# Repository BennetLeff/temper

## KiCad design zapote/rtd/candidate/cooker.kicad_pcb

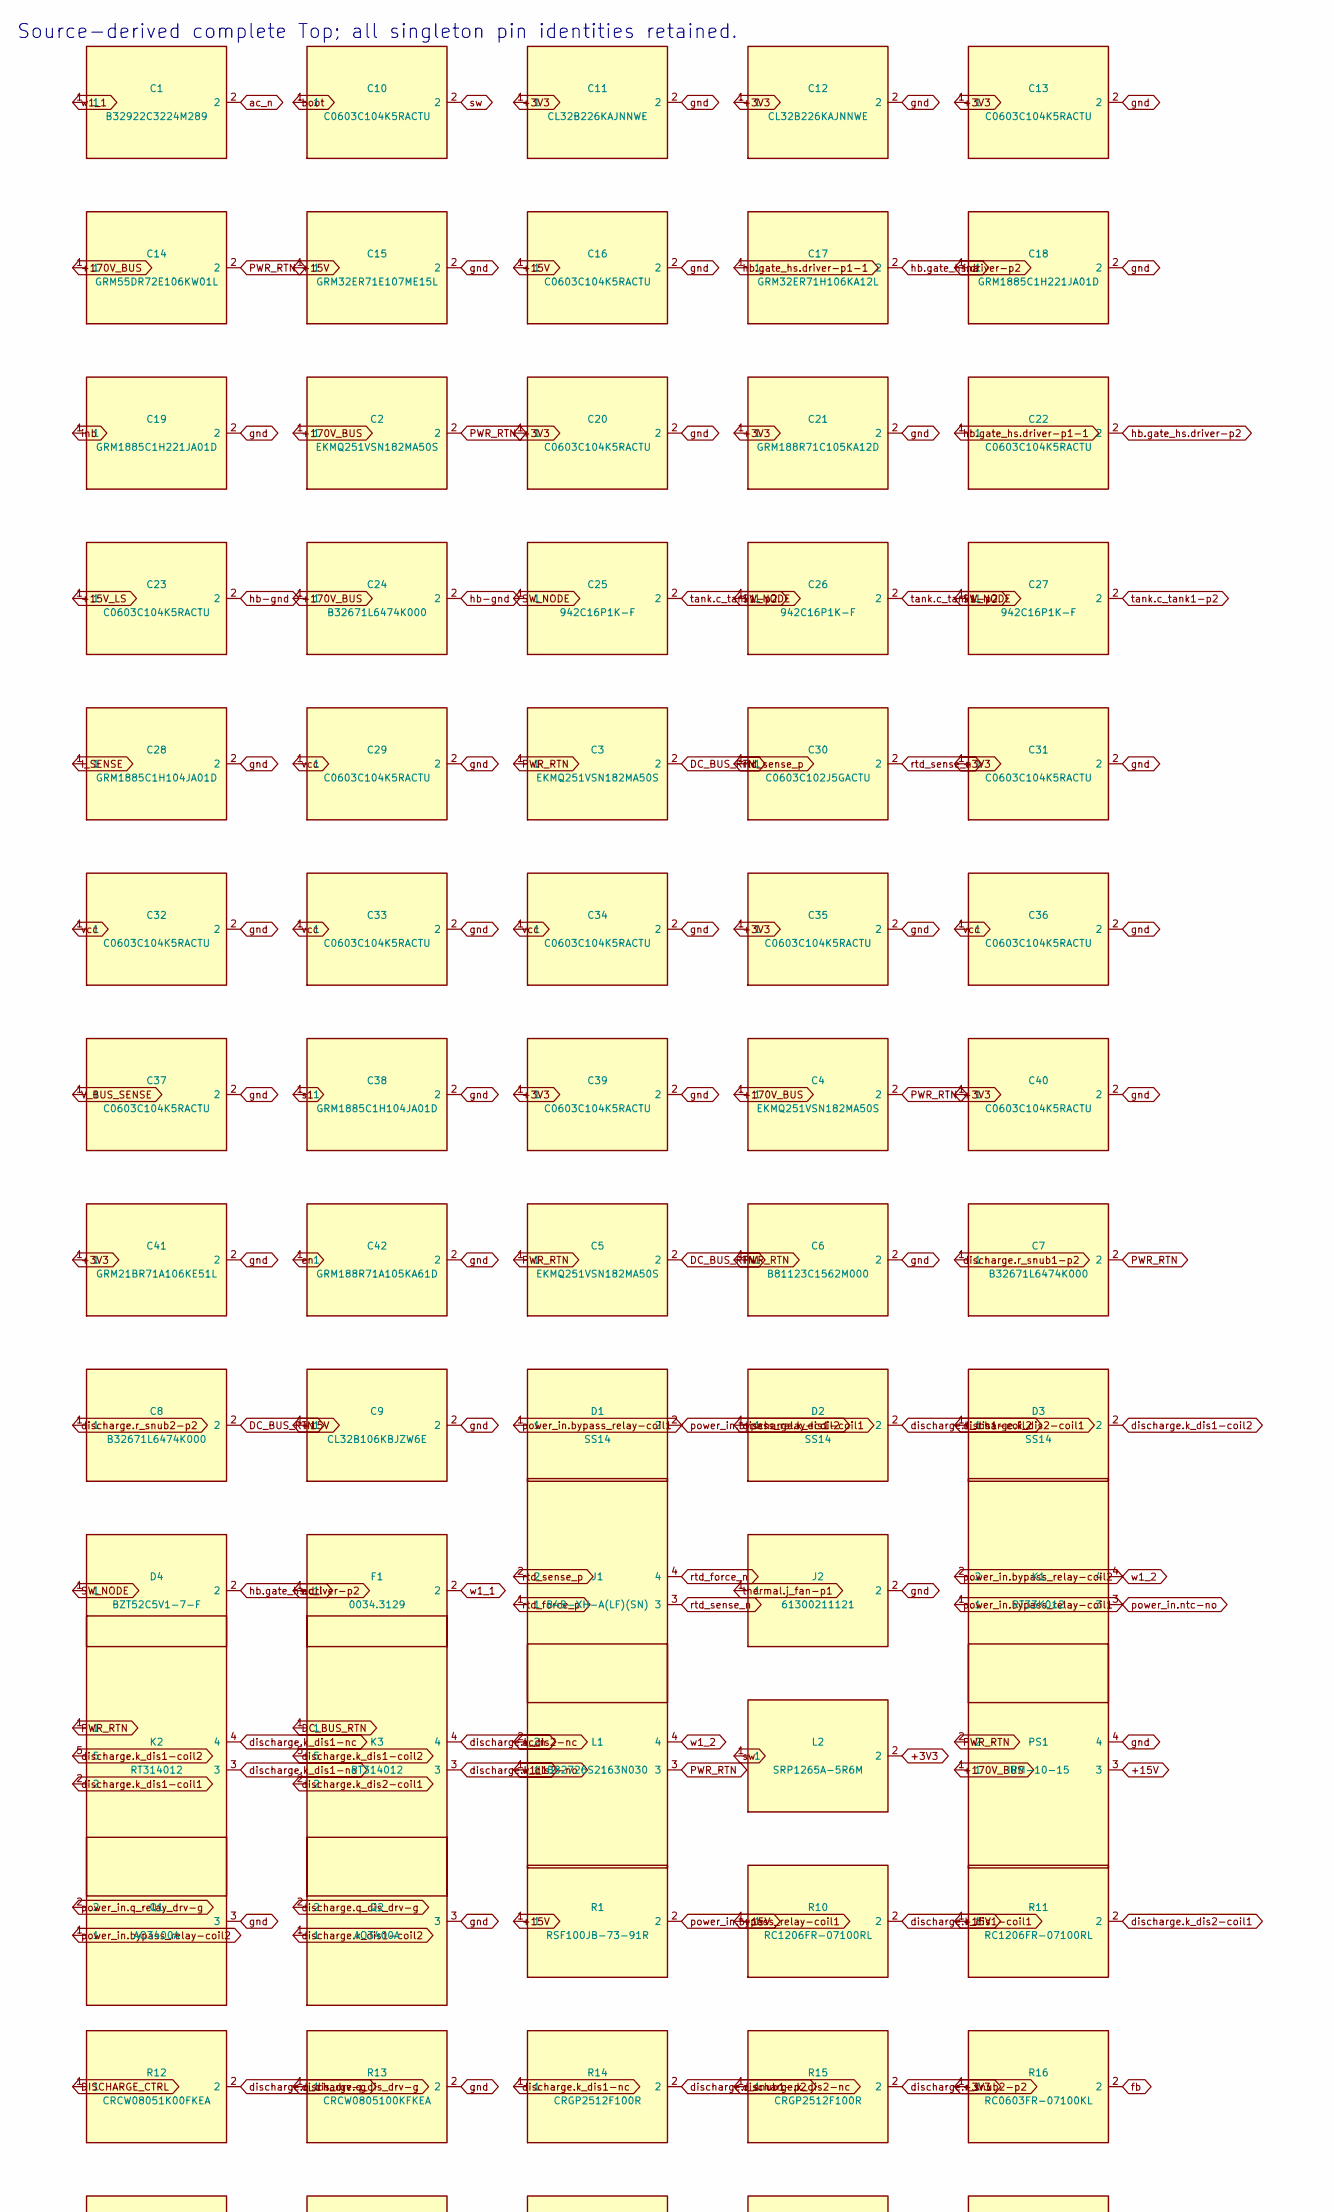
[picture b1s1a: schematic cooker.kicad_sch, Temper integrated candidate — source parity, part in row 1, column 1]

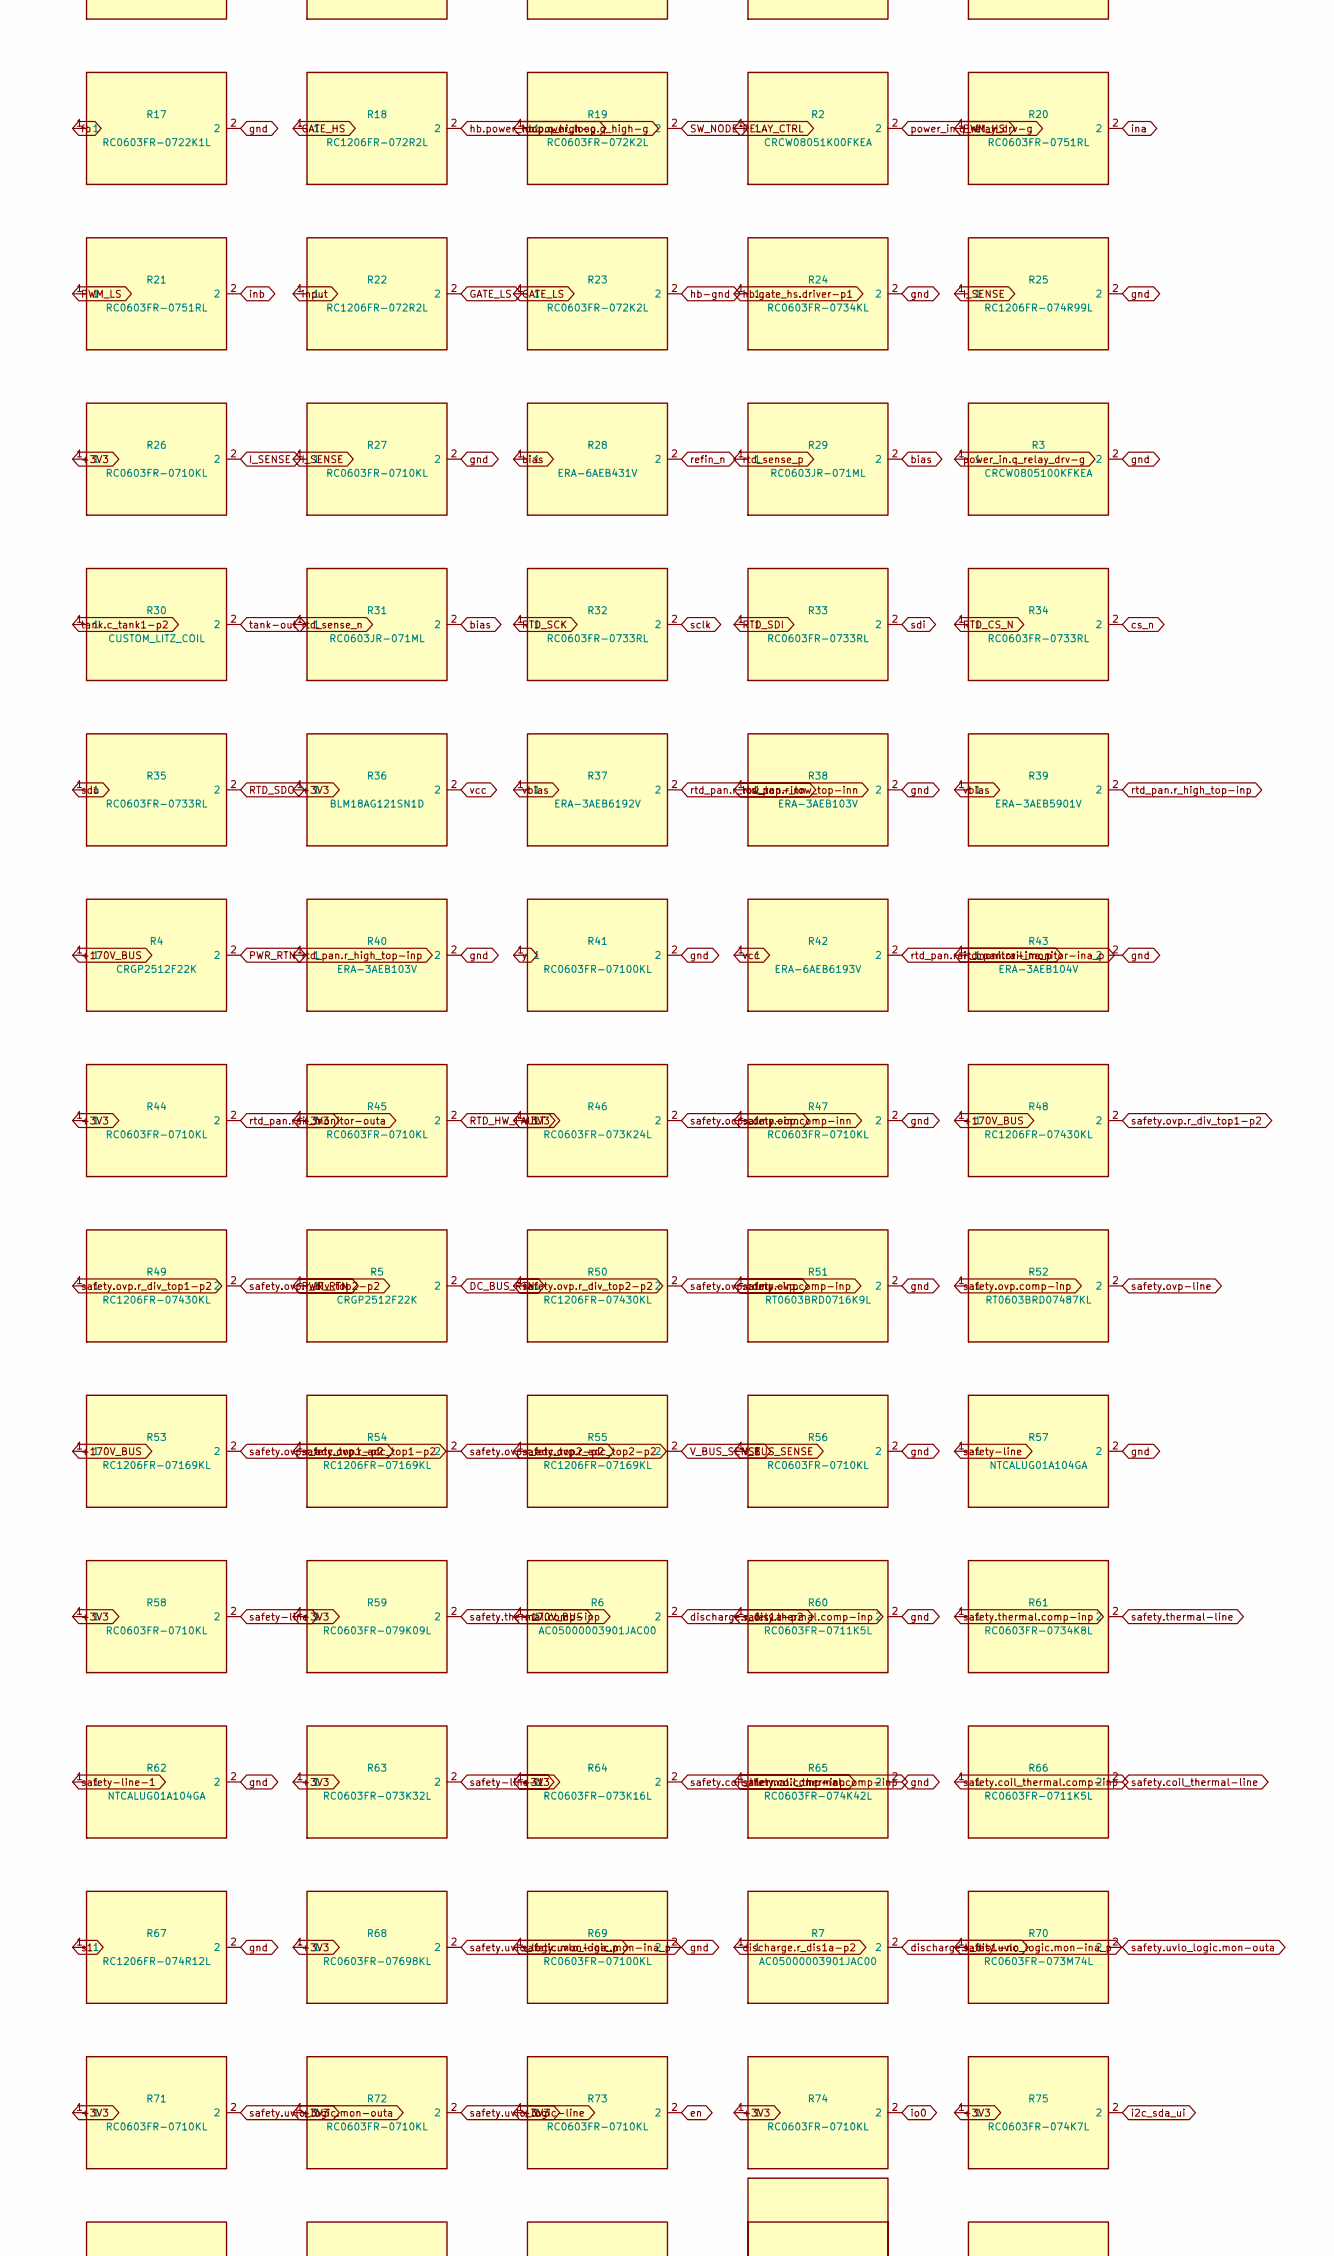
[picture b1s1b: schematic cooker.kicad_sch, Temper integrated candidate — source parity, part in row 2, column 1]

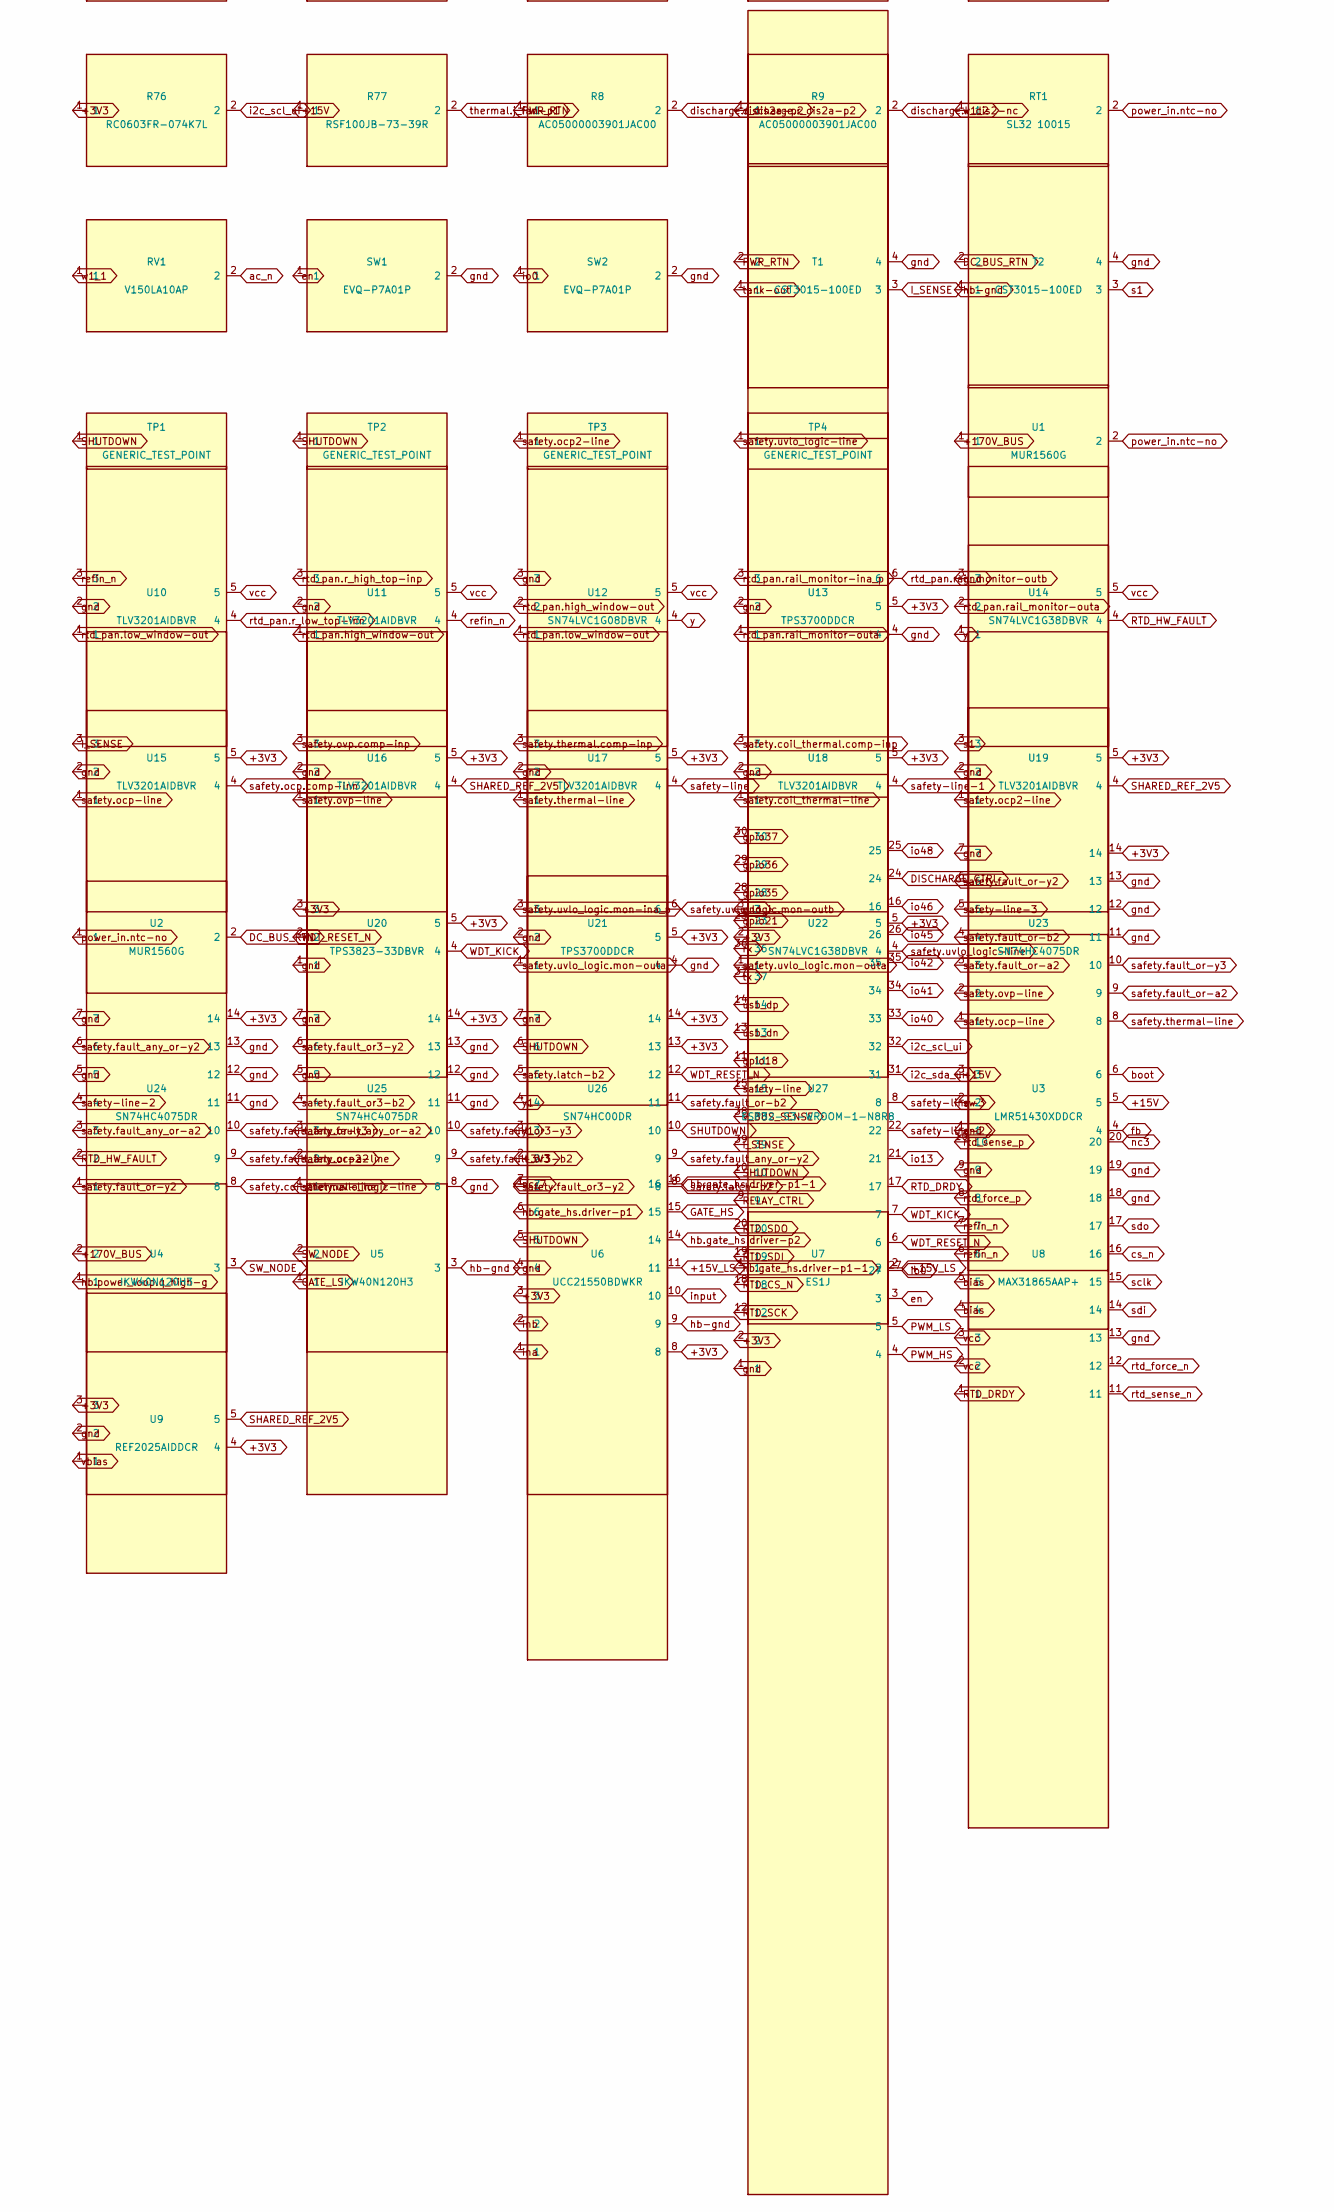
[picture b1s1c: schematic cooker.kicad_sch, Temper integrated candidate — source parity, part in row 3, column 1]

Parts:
C1: B32922C3224M289; C_Rect_L18.0mm_W7.0mm_P15.00mm_FKS3_FKP3
C2, C3, C4, C5: EKMQ251VSN182MA50S; CP_Radial_D35.0mm_P10.00mm_SnapIn
C6: B81123C1562M000; C_Rect_L26.5mm_W7.0mm_P22.50mm_MKS4
C7, C8, C24: B32671L6474K000; C_Rect_L18.0mm_W11.0mm_P15.00mm_FKS3_FKP3
C9: CL32B106KBJZW6E; C_1210_3225Metric
C10, C13, C16, C20, C22, C23, C29, C31, C32, C33, C34, C35, C36, C37, C39, C40: C0603C104K5RACTU; C_0603_1608Metric
C11, C12: CL32B226KAJNNWE; C_1210_3225Metric
C14: GRM55DR72E106KW01L; C_2220_5750Metric
C15: GRM32ER71E107ME15L; C_1210_3225Metric
C17: GRM32ER71H106KA12L; C_1210_3225Metric
C18, C19: GRM1885C1H221JA01D; C_0603_1608Metric
C21: GRM188R71C105KA12D; C_0603_1608Metric
C25, C26, C27: 942C16P1K-F; C_Axial_L34.0mm_D22.5mm_P40.00mm_Horizontal
C28, C38: GRM1885C1H104JA01D; C_0603_1608Metric
C30: C0603C102J5GACTU; C_0603_1608Metric
C41: GRM21BR71A106KE51L; C_0805_2012Metric
C42: GRM188R71A105KA61D; C_0603_1608Metric
D1, D2, D3: SS14; D_SMA
D4: BZT52C5V1-7-F; D_SOD-123
F1: 0034.3129; Fuse_Holder_5x20mm
J1: B4B-XH-A(LF)(SN); JST_XH_B4B-XH-A_1x04_P2.50mm_Vertical
J2: 61300211121; PinHeader_1x02_P2.54mm_Vertical
K1: RT33K012; Relay_SPST_Schrack-RT33K012
K2, K3: RT314012; Relay_SPDT_Schrack-RT314012
L1: B82726S2163N030; CMC_B82726S
L2: SRP1265A-5R6M; L_Bourns_SRP1265A
PS1: IRM-10-15; Converter_ACDC_MeanWell_IRM-10-xx_THT
Q1, Q2: AO3400A; SOT-23
R1: RSF100JB-73-91R; R_Axial_DIN0207_L6.3mm_D2.5mm_P10.16mm_Horizontal
R2, R12: CRCW08051K00FKEA; R_0805_2012Metric
R3, R13: CRCW0805100KFKEA; R_0805_2012Metric
R4, R5: CRGP2512F22K; R_2512_6332Metric
R6, R7, R8, R9: AC05000003901JAC00; R_Axial_DIN0918_L18.0mm_D9.0mm_P22.86mm_Horizontal
R10, R11: RC1206FR-07100RL; R_1206_3216Metric
R14, R15: CRGP2512F100R; R_2512_6332Metric
R16, R41, R69: RC0603FR-07100KL; R_0603_1608Metric
R17: RC0603FR-0722K1L; R_0603_1608Metric
R18, R22: RC1206FR-072R2L; R_1206_3216Metric
R19, R23: RC0603FR-072K2L; R_0603_1608Metric
R20, R21: RC0603FR-0751RL; R_0603_1608Metric
R24: RC0603FR-0734KL; R_0603_1608Metric
R25: RC1206FR-074R99L; R_1206_3216Metric
R26, R27, R44, R45, R47, R56, R58, R71, R72, R73, R74: RC0603FR-0710KL; R_0603_1608Metric
R28: ERA-6AEB431V; R_0805_2012Metric
R29, R31: RC0603JR-071ML; R_0603_1608Metric
R30: CUSTOM_LITZ_COIL; LitzPad_15A
R32, R33, R34, R35: RC0603FR-0733RL; R_0603_1608Metric
R36: BLM18AG121SN1D; L_0603_1608Metric
R37: ERA-3AEB6192V; R_0603_1608Metric
R38, R40: ERA-3AEB103V; R_0603_1608Metric
R39: ERA-3AEB5901V; R_0603_1608Metric
R42: ERA-6AEB6193V; R_0805_2012Metric
R43: ERA-3AEB104V; R_0603_1608Metric
R46: RC0603FR-073K24L; R_0603_1608Metric
R48, R49, R50: RC1206FR-07430KL; R_1206_3216Metric
R51: RT0603BRD0716K9L; R_0603_1608Metric
R52: RT0603BRD07487KL; R_0603_1608Metric
R53, R54, R55: RC1206FR-07169KL; R_1206_3216Metric
R57: NTCALUG01A104GA; R_Axial_DIN0204_L3.6mm_D1.6mm_P2.54mm_Vertical
R59: RC0603FR-079K09L; R_0603_1608Metric
R60, R66: RC0603FR-0711K5L; R_0603_1608Metric
R61: RC0603FR-0734K8L; R_0603_1608Metric
R62: NTCALUG01A104GA; R_Axial_DIN0207_L6.3mm_D2.5mm_P10.16mm_Horizontal
R63: RC0603FR-073K32L; R_0603_1608Metric
R64: RC0603FR-073K16L; R_0603_1608Metric
R65: RC0603FR-074K42L; R_0603_1608Metric
R67: RC1206FR-074R12L; R_1206_3216Metric
R68: RC0603FR-07698KL; R_0603_1608Metric
R70: RC0603FR-073M74L; R_0603_1608Metric
R75, R76: RC0603FR-074K7L; R_0603_1608Metric
R77: RSF100JB-73-39R; R_Axial_DIN0207_L6.3mm_D2.5mm_P10.16mm_Horizontal
RT1: SL32 10015; R_Disc_D15.0mm_W7.0mm_P7.5mm
RV1: V150LA10AP; RV_Disc_D15.5mm_W5.2mm_P7.5mm
SW1, SW2: EVQ-P7A01P; SW_SPST_EVQP7A
T1, T2: CST3015-100ED; CST3015
TP1, TP2, TP3, TP4: GENERIC_TEST_POINT; TestPoint_Pad_D1.0mm
U1, U2: MUR1560G; TO-220-2_Vertical
U3: LMR51430XDDCR; SOT-23-6
U4, U5: IKW40N120H3; TO-247-3_Vertical
U6: UCC21550BDWKR; SOIC16W_Isolated
U7: ES1J; D_SMA
U8: MAX31865AAP+; SSOP-20_3.9x8.7mm_P0.635mm
U9: REF2025AIDDCR; SOT-23-5
U10, U11, U15, U16, U17, U18, U19: TLV3201AIDBVR; SOT-23-5
U12: SN74LVC1G08DBVR; SOT-23-5
U13, U21: TPS3700DDCR; SOT-23-6
U14, U22: SN74LVC1G38DBVR; SOT-23-5
U20: TPS3823-33DBVR; SOT-23-5
U23, U24, U25: SN74HC4075DR; SOIC-14_3.9x8.7mm_P1.27mm
U26: SN74HC00DR; SOIC-14_3.9x8.7mm_P1.27mm
U27: ESP32-S3-WROOM-1-N8R8; ESP32-S3-WROOM-1

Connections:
+3V3: C11.1, C12.1, C13.1, C20.1, C21.1, C31.1, C35.1, C39.1, C40.1, C41.1, L2.2, R16.1, R26.1, R36.1, R44.1, R45.1, R46.1, R58.1, R59.1, R63.1, R64.1, R68.1, R71.1, R72.1, R73.1, R74.1, R75.1, R76.1, U6.3, U6.8, U9.3, U9.4, U13.5, U15.5, U16.5, U17.5, U18.5, U19.5, U20.3, U20.5, U21.5, U22.2, U22.5, U23.14, U24.14, U25.14, U26.2, U26.13, U26.14, U27.2
+15V: C9.1, C15.1, C16.1, PS1.3, R1.1, R10.1, R11.1, R77.1, U3.3, U3.5
+15V_LS: C23.1, U6.11, U7.2
+170V_BUS: C2.1, C4.1, C14.1, C24.1, PS1.1, R4.1, R6.1, R48.1, R53.1, U1.1, U4.2
DC_BUS_RTN: C3.2, C5.2, C8.2, K3.1, R5.2, T2.2, U2.2
DISCHARGE_CTRL: R12.1, U27.24
GATE_HS: R18.1, U6.15
GATE_LS: R22.2, R23.1, U5.1
I_SENSE: C28.1, R25.1, R26.2, R27.1, T1.3, U15.3, U27.39
PWM_HS: R20.1, U27.4
PWM_LS: R21.1, U27.5
PWR_RTN: C2.2, C3.1, C4.2, C5.1, C6.1, C7.2, C14.2, K2.1, L1.3, PS1.2, R4.2, R5.1, R8.1, T1.2
RELAY_CTRL: R2.1, U27.9
RTD_CS_N: R34.1, U27.18
RTD_DRDY: U8.1, U27.17
RTD_HW_FAULT: R45.2, U14.4, U24.2
RTD_SCK: R32.1, U27.12
RTD_SDI: R33.1, U27.19
RTD_SDO: R35.2, U27.20
SHARED_REF_2V5: U9.5, U16.4, U19.4
SHUTDOWN: TP1.1, TP2.1, U6.5, U26.6, U26.10, U27.10
SW_NODE: C25.1, C26.1, C27.1, D4.1, R19.2, U4.3, U5.2
V_BUS_SENSE: C37.1, R55.2, R56.1, U27.38
WDT_KICK: U20.4, U27.7
WDT_RESET_N: U20.2, U26.12, U27.6
ac_l: F1.1
ac_n: C1.2, L1.2, RV1.2
bias: R28.1, R29.2, R31.2, U8.4, U8.5
boot: C10.1, U3.6
cs_n: R34.2, U8.16
discharge.k_dis1-coil1: D2.1, K2.2, R10.2
discharge.k_dis1-coil2: D2.2, D3.2, K2.5, K3.5, Q2.1
discharge.k_dis1-nc: K2.4, R7.2, R14.1
discharge.k_dis1-no: K2.3
discharge.k_dis2-coil1: D3.1, K3.2, R11.2
discharge.k_dis2-nc: K3.4, R9.2, R15.1
discharge.k_dis2-no: K3.3
discharge.q_dis_drv-g: Q2.2, R12.2, R13.1
discharge.r_dis1a-p2: R6.2, R7.1
discharge.r_dis2a-p2: R8.2, R9.1
discharge.r_snub1-p2: C7.1, R14.2
discharge.r_snub2-p2: C8.1, R15.2
en: C42.1, R73.2, SW1.1, U27.3
fb: R16.2, R17.1, U3.4
gnd: C6.2, C9.2, C11.2, C12.2, C13.2, C15.2, C16.2, C18.2, C19.2, C20.2, C21.2, C28.2, C29.2, C31.2, C32.2, C33.2, C34.2, C35.2, C36.2, C37.2, C38.2, C39.2, C40.2, C41.2, C42.2, J2.2, PS1.4, Q1.3, Q2.3, R3.2, R13.2, R17.2, R24.2, R25.2, R27.2, R38.2, R40.2, R41.2, R43.2, R47.2, R51.2, R56.2, R57.2, R60.2, R62.2, R65.2, R67.2, R69.2, SW1.2, SW2.2, T1.4, T2.4, U3.1, U6.4, U8.9, U8.13, U8.18, U8.19, U9.2, U10.2, U11.2, U12.3, U13.2, U13.4, U14.3, U15.2, U16.2, U17.2, U18.2, U19.2, U20.1, U21.2, U21.4, U22.3, U23.7, U23.11, U23.12, U23.13, U24.5, U24.7, U24.11, U24.12, U24.13, U25.5, U25.7, U25.8, U25.11, U25.12, U25.13, U26.7, U27.1
gpio18: U27.11
gpio21: U27.23
gpio35: U27.28
gpio36: U27.29
gpio37: U27.30
hb-gnd: C23.2, C24.2, R23.2, T2.1, U5.3, U6.9
hb.gate_hs.driver-p1: R24.1, U6.6
hb.gate_hs.driver-p1-1: C17.1, C22.1, U6.16, U7.1
hb.gate_hs.driver-p2: C17.2, C22.2, D4.2, U6.14
hb.power_loop.q_high-g: R18.2, R19.1, U4.1
i2c_scl_ui: R76.2, U27.32
i2c_sda_ui: R75.2, U27.31
ina: C18.1, R20.2, U6.1
inb: C19.1, R21.2, U6.2
input: R22.1, U6.10
io0: R74.2, SW2.1, U27.27
io13: U27.21
io40: U27.33
io41: U27.34
io42: U27.35
io45: U27.26
io46: U27.16
io48: U27.25
nc3: U8.20
nc_7: U6.7
power_in.bypass_relay-coil1: D1.1, K1.1, R1.2
power_in.bypass_relay-coil2: D1.2, K1.2, Q1.1
power_in.ntc-no: K1.3, RT1.2, U1.2, U2.1
power_in.q_relay_drv-g: Q1.2, R2.2, R3.1
refin_n: R28.2, U8.6, U8.7, U10.3, U11.4
rtd_force_n: J1.4, U8.12
rtd_force_p: J1.1, U8.8
rtd_pan.high_window-out: U11.1, U12.2
rtd_pan.low_window-out: U10.1, U12.1
rtd_pan.r_high_top-inp: R39.2, R40.1, U11.3
rtd_pan.r_low_top-inn: R37.2, R38.1, U10.4
rtd_pan.rail_monitor-ina_p: R42.2, R43.1, U13.3
rtd_pan.rail_monitor-outa: R44.2, U13.1, U14.2
rtd_pan.rail_monitor-outb: U13.6
rtd_sense_n: C30.2, J1.3, R31.1, U8.11
rtd_sense_p: C30.1, J1.2, R29.1, U8.10
rx: U27.36
s1: C38.1, R67.1, T2.3, U19.3
safety-line: R57.1, R58.2, U17.4, U27.15
safety-line-1: R62.1, R63.2, U18.4
safety-line-2: U24.4, U27.22
safety-line-3: U23.5, U27.8
safety.coil_thermal-line: R66.2, U18.1, U24.8
safety.coil_thermal.comp-inp: R64.2, R65.1, R66.1, U18.3
safety.fault_any_or-a2: U24.3, U24.9, U25.3
safety.fault_any_or-y2: U24.6, U26.9
safety.fault_any_or-y3: U24.10
safety.fault_or3-b2: U25.4, U25.9
safety.fault_or3-y2: U25.6, U26.1
safety.fault_or3-y3: U25.10
safety.fault_or-a2: U23.3, U23.9
safety.fault_or-b2: U23.4, U26.11
safety.fault_or-y2: U23.6, U24.1
safety.fault_or-y3: U23.10
safety.latch-b2: U26.5, U26.8
safety.ocp2-line: TP3.1, U19.1, U25.2
safety.ocp-line: U15.1, U23.1
safety.ocp.comp-inn: R46.2, R47.1, U15.4
safety.ovp-line: R52.2, U16.1, U23.2
safety.ovp.comp-inp: R50.2, R51.1, R52.1, U16.3
safety.ovp.r_adc_top1-p2: R53.2, R54.1
safety.ovp.r_adc_top2-p2: R54.2, R55.1
safety.ovp.r_div_top1-p2: R48.2, R49.1
safety.ovp.r_div_top2-p2: R49.2, R50.1
safety.thermal-line: R61.2, U17.1, U23.8
safety.thermal.comp-inp: R59.2, R60.1, R61.1, U17.3
safety.uvlo_logic-line: R72.2, TP4.1, U22.4, U25.1
safety.uvlo_logic.mon-ina_p: R68.2, R69.1, R70.1, U21.3
safety.uvlo_logic.mon-outa: R70.2, R71.2, U21.1, U22.1
safety.uvlo_logic.mon-outb: U21.6
sclk: R32.2, U8.15
sdi: R33.2, U8.14
sdo: R35.1, U8.17
sw: C10.2, L2.1, U3.2
tank-out: R30.2, T1.1
tank.c_tank1-p2: C25.2, C26.2, C27.2, R30.1
thermal.j_fan-p1: J2.1, R77.2
tx: U27.37
usb_dn: U27.13
usb_dp: U27.14
vbias: R37.1, R39.1, U9.1
vcc: C29.1, C32.1, C33.1, C34.1, C36.1, R36.2, R42.1, U8.2, U8.3, U10.5, U11.5, U12.5, U14.5
w1_1: C1.1, F1.2, L1.1, RV1.1
w1_2: K1.4, L1.4, RT1.1
y: R41.1, U12.4, U14.1
y1: U26.3, U26.4

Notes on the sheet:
Source-derived complete Top; all singleton pin identities retained.

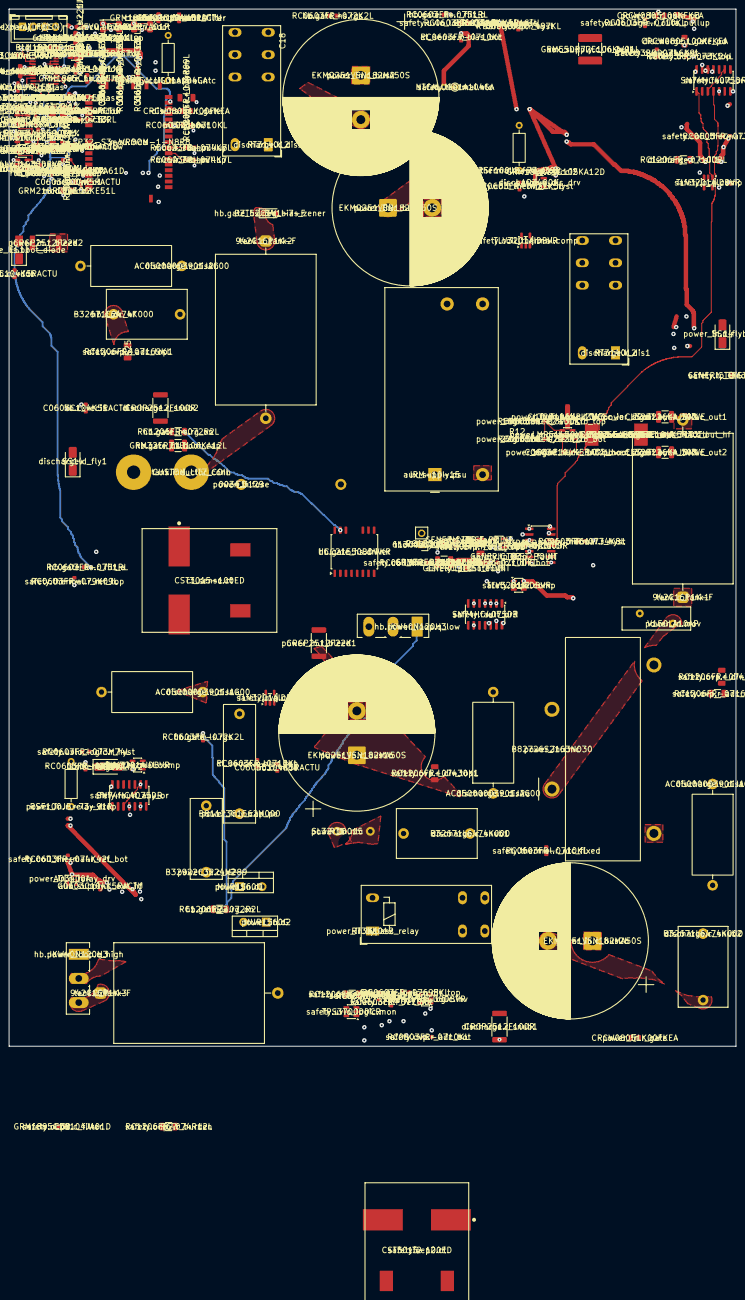
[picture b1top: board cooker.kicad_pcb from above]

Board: 6 copper layers, 164.0 x 234.0 mm, 171 parts (0 on the bottom side), 110 nets.

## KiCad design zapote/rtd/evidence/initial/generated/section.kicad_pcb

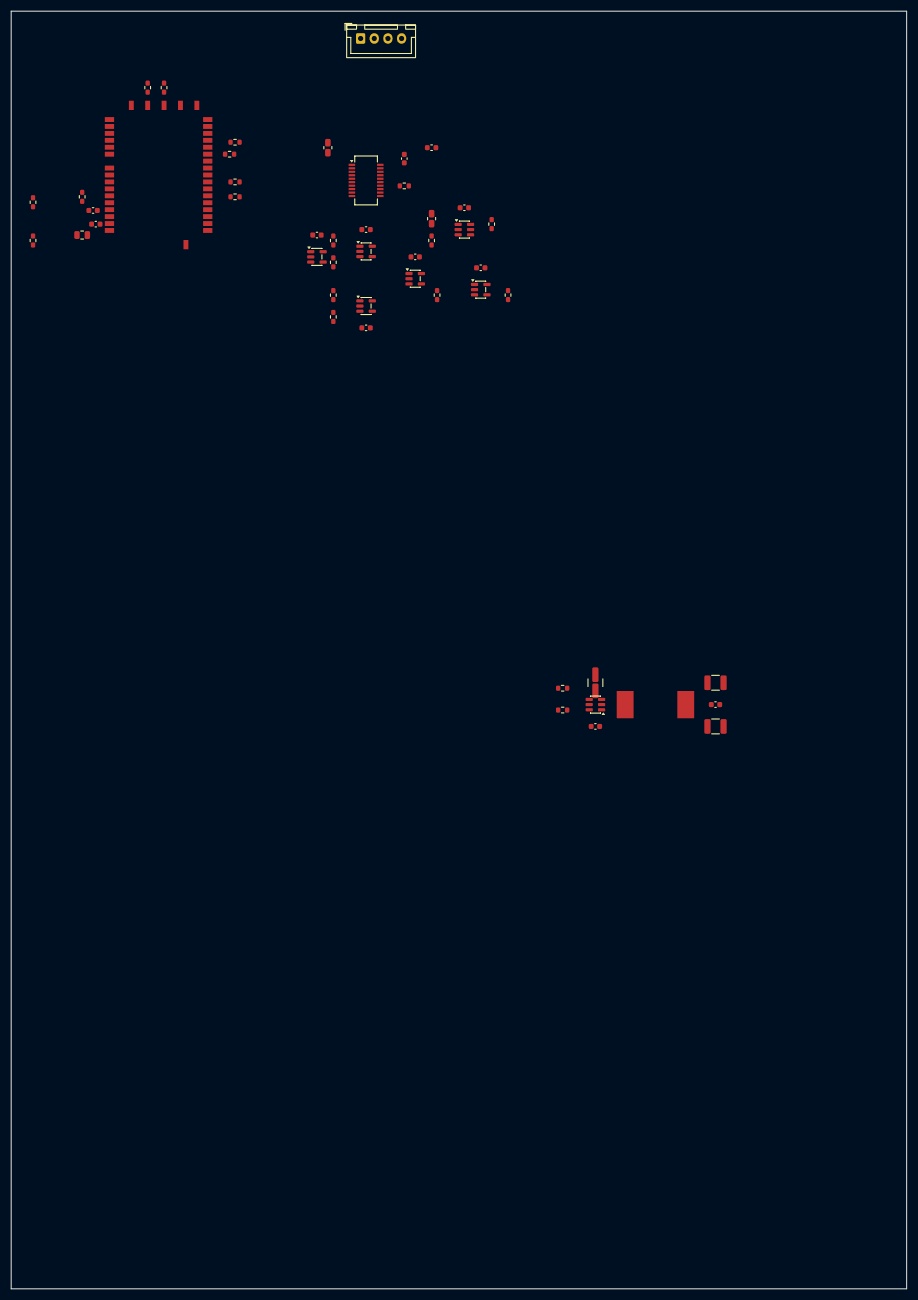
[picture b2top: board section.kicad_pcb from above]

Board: 6 copper layers, 164.0 x 234.0 mm, 49 parts (0 on the bottom side), 35 nets, no tracks yet.

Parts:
C9: 10uF +/- 10%; C_1210_3225Metric
C10, C13: 100nF +/- 10%; C_0603_1608Metric
C11, C12: 22uF +/- 10%; C_1210_3225Metric
C29, C30, C31, C32, C33, C34, C35, C39: 100nF; C_0603_1608Metric
C40: 10uF; C_0805_2012Metric
C41: 1uF +/- 10%; C_0603_1608Metric
J1: B4B-XH-A(LF)(SN); JST_XH_B4B-XH-A_1x04_P2.50mm_Vertical
L2: 5.6uH; L_Bourns_SRP1265A
R16, R39: 100kohm +/- 1%; R_0603_1608Metric
R17: 22.1kohm +/- 1%; R_0603_1608Metric
R28: 430ohm +/- 0.1%; R_0805_2012Metric
R29, R31, R32, R33: 33ohm +/- 5%; R_0603_1608Metric
R34: 120ohm; L_0603_1608Metric
R35: 61.9kohm +/- 0.1%; R_0603_1608Metric
R36, R38: 10kohm +/- 0.1%; R_0603_1608Metric
R37: 5.9kohm +/- 0.1%; R_0603_1608Metric
R40: 619kohm +/- 0.1%; R_0805_2012Metric
R41: 100kohm +/- 0.1%; R_0603_1608Metric
R42, R43: 10kohm +/- 1%; R_0603_1608Metric
R71: 10kohm +/- 2%; R_0603_1608Metric
R72: 10kohm; R_0603_1608Metric
R73, R74: 4.7kohm; R_0603_1608Metric
SW1, SW2: EVQ-P7A01P; R_0603_1608Metric
U3: LMR51430XDDCR; SOT-23-6
U8: MAX31865AAP+; SSOP-20_3.9x8.7mm_P0.635mm
U9: REF2025AIDDCR; SOT-23-5
U10, U11: TLV3201AIDBVR; SOT-23-5
U12: SN74LVC1G08DBVR; SOT-23-5
U13: TPS3700DDCR; SOT-23-6
U14: SN74LVC1G38DBVR; SOT-23-5
U27: ESP32-S3-WROOM-1-N8R8; ESP32-S3-WROOM-1

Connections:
+3V3: C11.1, C12.1, C13.1, C30.1, C34.1, C39.1, C40.1, L2.2, R16.1, R34.1, R42.1, R43.1, R71.1, R72.1, R73.1, R74.1, U9.3, U9.4, U13.5, U27.2
+15V: C9.1, U3.3, U3.5
RTD_CS_N: R32.1, U27.18
RTD_DRDY: U8.1, U27.17
RTD_HW_FAULT: R43.2, U14.4
RTD_SCK: R29.1, U27.12
RTD_SDI: R31.1, U27.19
RTD_SDO: R33.2, U27.20
bias: R28.1, U8.4, U8.5
boot: C10.1, U3.6
cs_n: R32.2, U8.16
en: C41.1, R71.2, SW1.1, U27.3
fb: R16.2, R17.1, U3.4
gnd: C9.2, C11.2, C12.2, C13.2, C29.2, C30.2, C31.2, C32.2, C33.2, C34.2, C35.2, C39.2, C40.2, C41.2, R17.2, R36.2, R38.2, R39.2, R41.2, SW1.2, SW2.2, U3.1, U8.9, U8.13, U8.18, U8.19, U9.2, U10.2, U11.2, U12.3, U13.2, U13.4, U14.3, U27.1
i2c_scl_ui: R74.2, U27.32
i2c_sda_ui: R73.2, U27.31
io0: R72.2, SW2.1, U27.27
refin_n: R28.2, U8.6, U8.7, U10.3, U11.4
rtd_force_n: J1.4, U8.12
rtd_force_p: J1.1, U8.8
rtd_pan.high_window-out: U11.1, U12.2
rtd_pan.low_window-out: U10.1, U12.1
rtd_pan.r_high_top-inp: R37.2, R38.1, U11.3
rtd_pan.r_low_top-inn: R35.2, R36.1, U10.4
rtd_pan.rail_monitor-ina_p: R40.2, R41.1, U13.3
rtd_pan.rail_monitor-outa: R42.2, U13.1, U14.2
rtd_sense_n: J1.3, U8.11
rtd_sense_p: J1.2, U8.10
sclk: R29.2, U8.15
sdi: R31.2, U8.14
sdo: R33.1, U8.17
sw: C10.2, L2.1, U3.2
vbias: R35.1, R37.1, U9.1
vcc: C29.1, C31.1, C32.1, C33.1, C35.1, R34.2, R40.1, U8.2, U8.3, U10.5, U11.5, U12.5, U14.5
y: R39.1, U12.4, U14.1
